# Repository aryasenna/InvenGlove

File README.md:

InvenGlove
==========

An initial prototype of a data glove system for Virtual Assembly. 

InvenGlove captures hand motion and finger flex respectively using Inertial Measurement Unit (IMU)  and flex sensors.  The gloves is to be interfaced with a PC that runs a small program (InvenGlove Connector). This program interprets the sensors readings into object rotation, translation and zoom control inside Autodesk Inventor.

Minimum hardware requirements (barebone):

1x Arduino Mini Pro

2x SpectraSymbol Flex Sensor

1x HC 05 Bluetooth Module

1x InvenSense MPU 9150 Breakout board

(see Eagle PCB schematics and the codes for now, proper documentation should be available soon.)

InvenGlove is part of capstone project on Dept. of Mechanical Engineering, Universitas Indonesia. Released under GNU GPL v3

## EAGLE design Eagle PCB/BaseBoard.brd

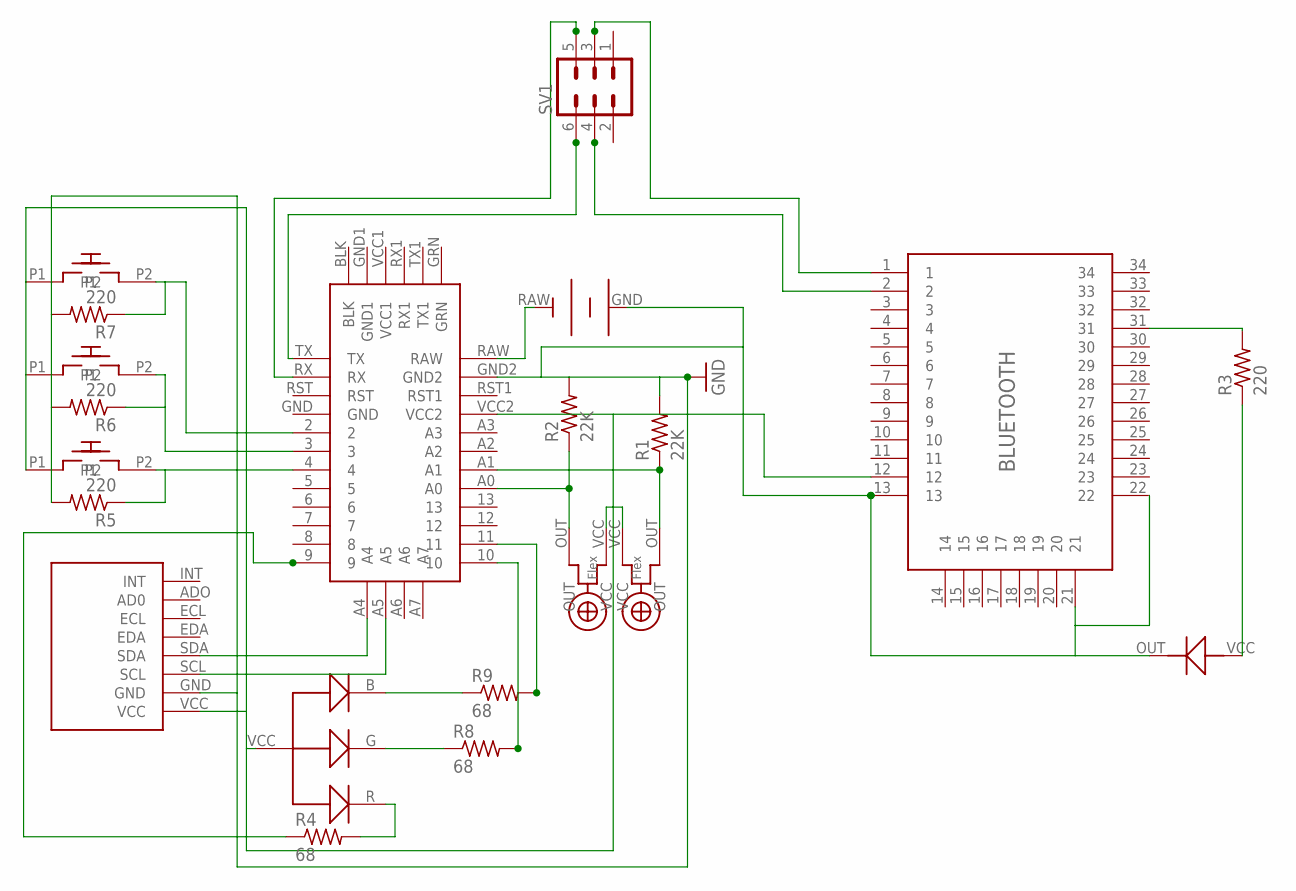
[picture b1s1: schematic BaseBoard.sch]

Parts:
BLUETOOTH-LED: LED; FLEX
R1, R2: 22K; R1206
R3, R5, R6, R7: 220; R1206
R4, R8, R9: 68; R1206
SV1: MA03-2
TOGGEL: PB
U$1: APM
U$2: MPU-9150
U$3, U$4: FLEX
U$5: BATT; BAT
U$6: BLUETOOTH
U$7: LED-RGB; LED
U$9, U$10: PB

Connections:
GND: BLUETOOTH-LED.OUT (1), R1.2, R2.2, R5.2, R6.2, R7.2, U$1.GND2, U$2.GND, U$5.GND, U$6.13, U$6.21, U$6.22
unnamed: U$1.A4, U$2.SDA
unnamed: U$1.A5, U$2.SCL
unnamed: R8.1, U$7.G
unnamed: R9.1, U$7.B
unnamed: TOGGEL.P1, U$1.VCC2, U$2.VCC, U$3.VCC, U$4.VCC, U$6.12, U$7.VCC, U$9.P1, U$10.P1
unnamed: R2.1, U$1.A0, U$3.OUT
unnamed: R1.1, U$1.A1, U$4.OUT
unnamed: U$1.RAW, U$5.RAW
unnamed: R4.2, U$7.R
unnamed: R3.2, U$6.31
unnamed: BLUETOOTH-LED.VCC (2), R3.1
unnamed: SV1.5, U$1.RX
unnamed: SV1.6, U$1.TX
unnamed: R4.1, U$1.9
unnamed: SV1.3, U$6.1
unnamed: SV1.4, U$6.2
unnamed: R9.2, U$1.11
unnamed: R8.2, U$1.10
unnamed: R5.1, TOGGEL.P2, U$1.4
unnamed: R6.1, U$1.3, U$9.P2
unnamed: R7.1, U$1.2, U$10.P2

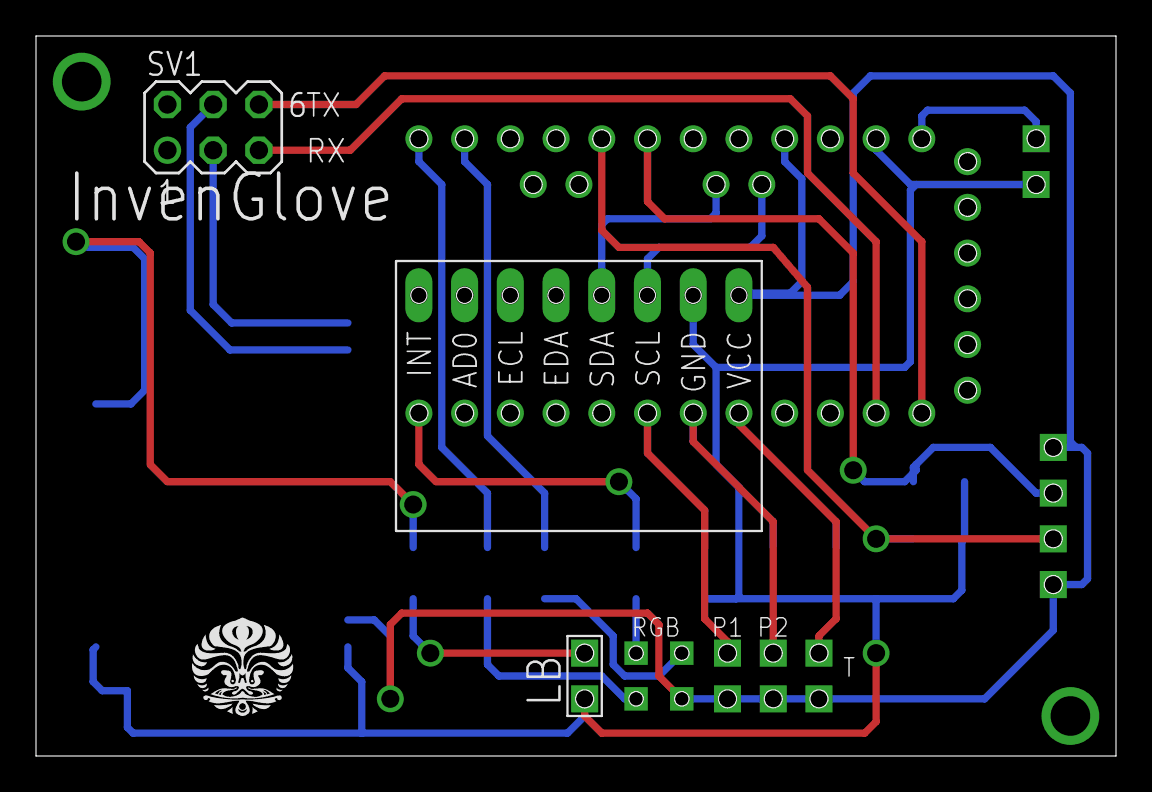
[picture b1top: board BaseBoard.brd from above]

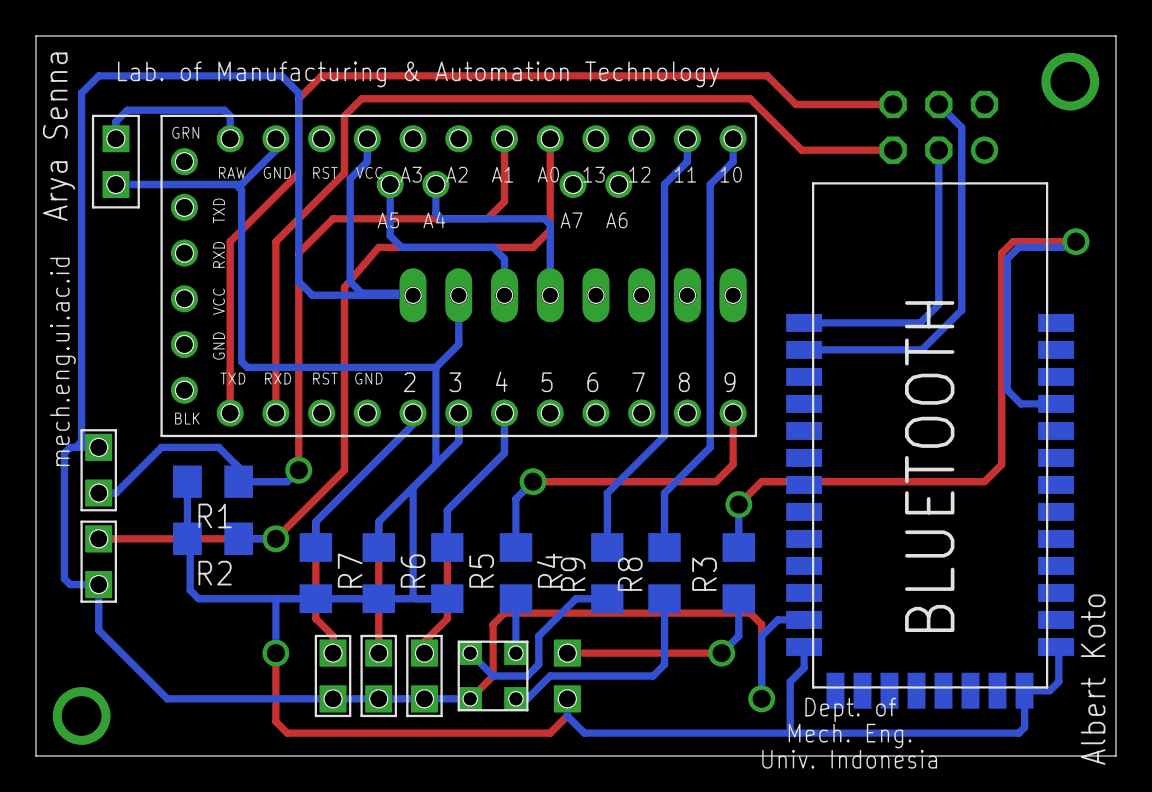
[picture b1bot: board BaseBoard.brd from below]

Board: 2 copper layers, 60.0 x 40.0 mm, 22 parts (19 on the bottom side), 22 nets.

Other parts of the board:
U$8: MAKARABOTTOM

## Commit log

2014-07-14 :boom::camel: Added .gitattributes & .gitignore files
2014-07-14 Initial uploads
2014-07-14 Readme created
2014-07-14 Add eagle baseboard files
2014-07-14 Create gh-pages branch via GitHub
